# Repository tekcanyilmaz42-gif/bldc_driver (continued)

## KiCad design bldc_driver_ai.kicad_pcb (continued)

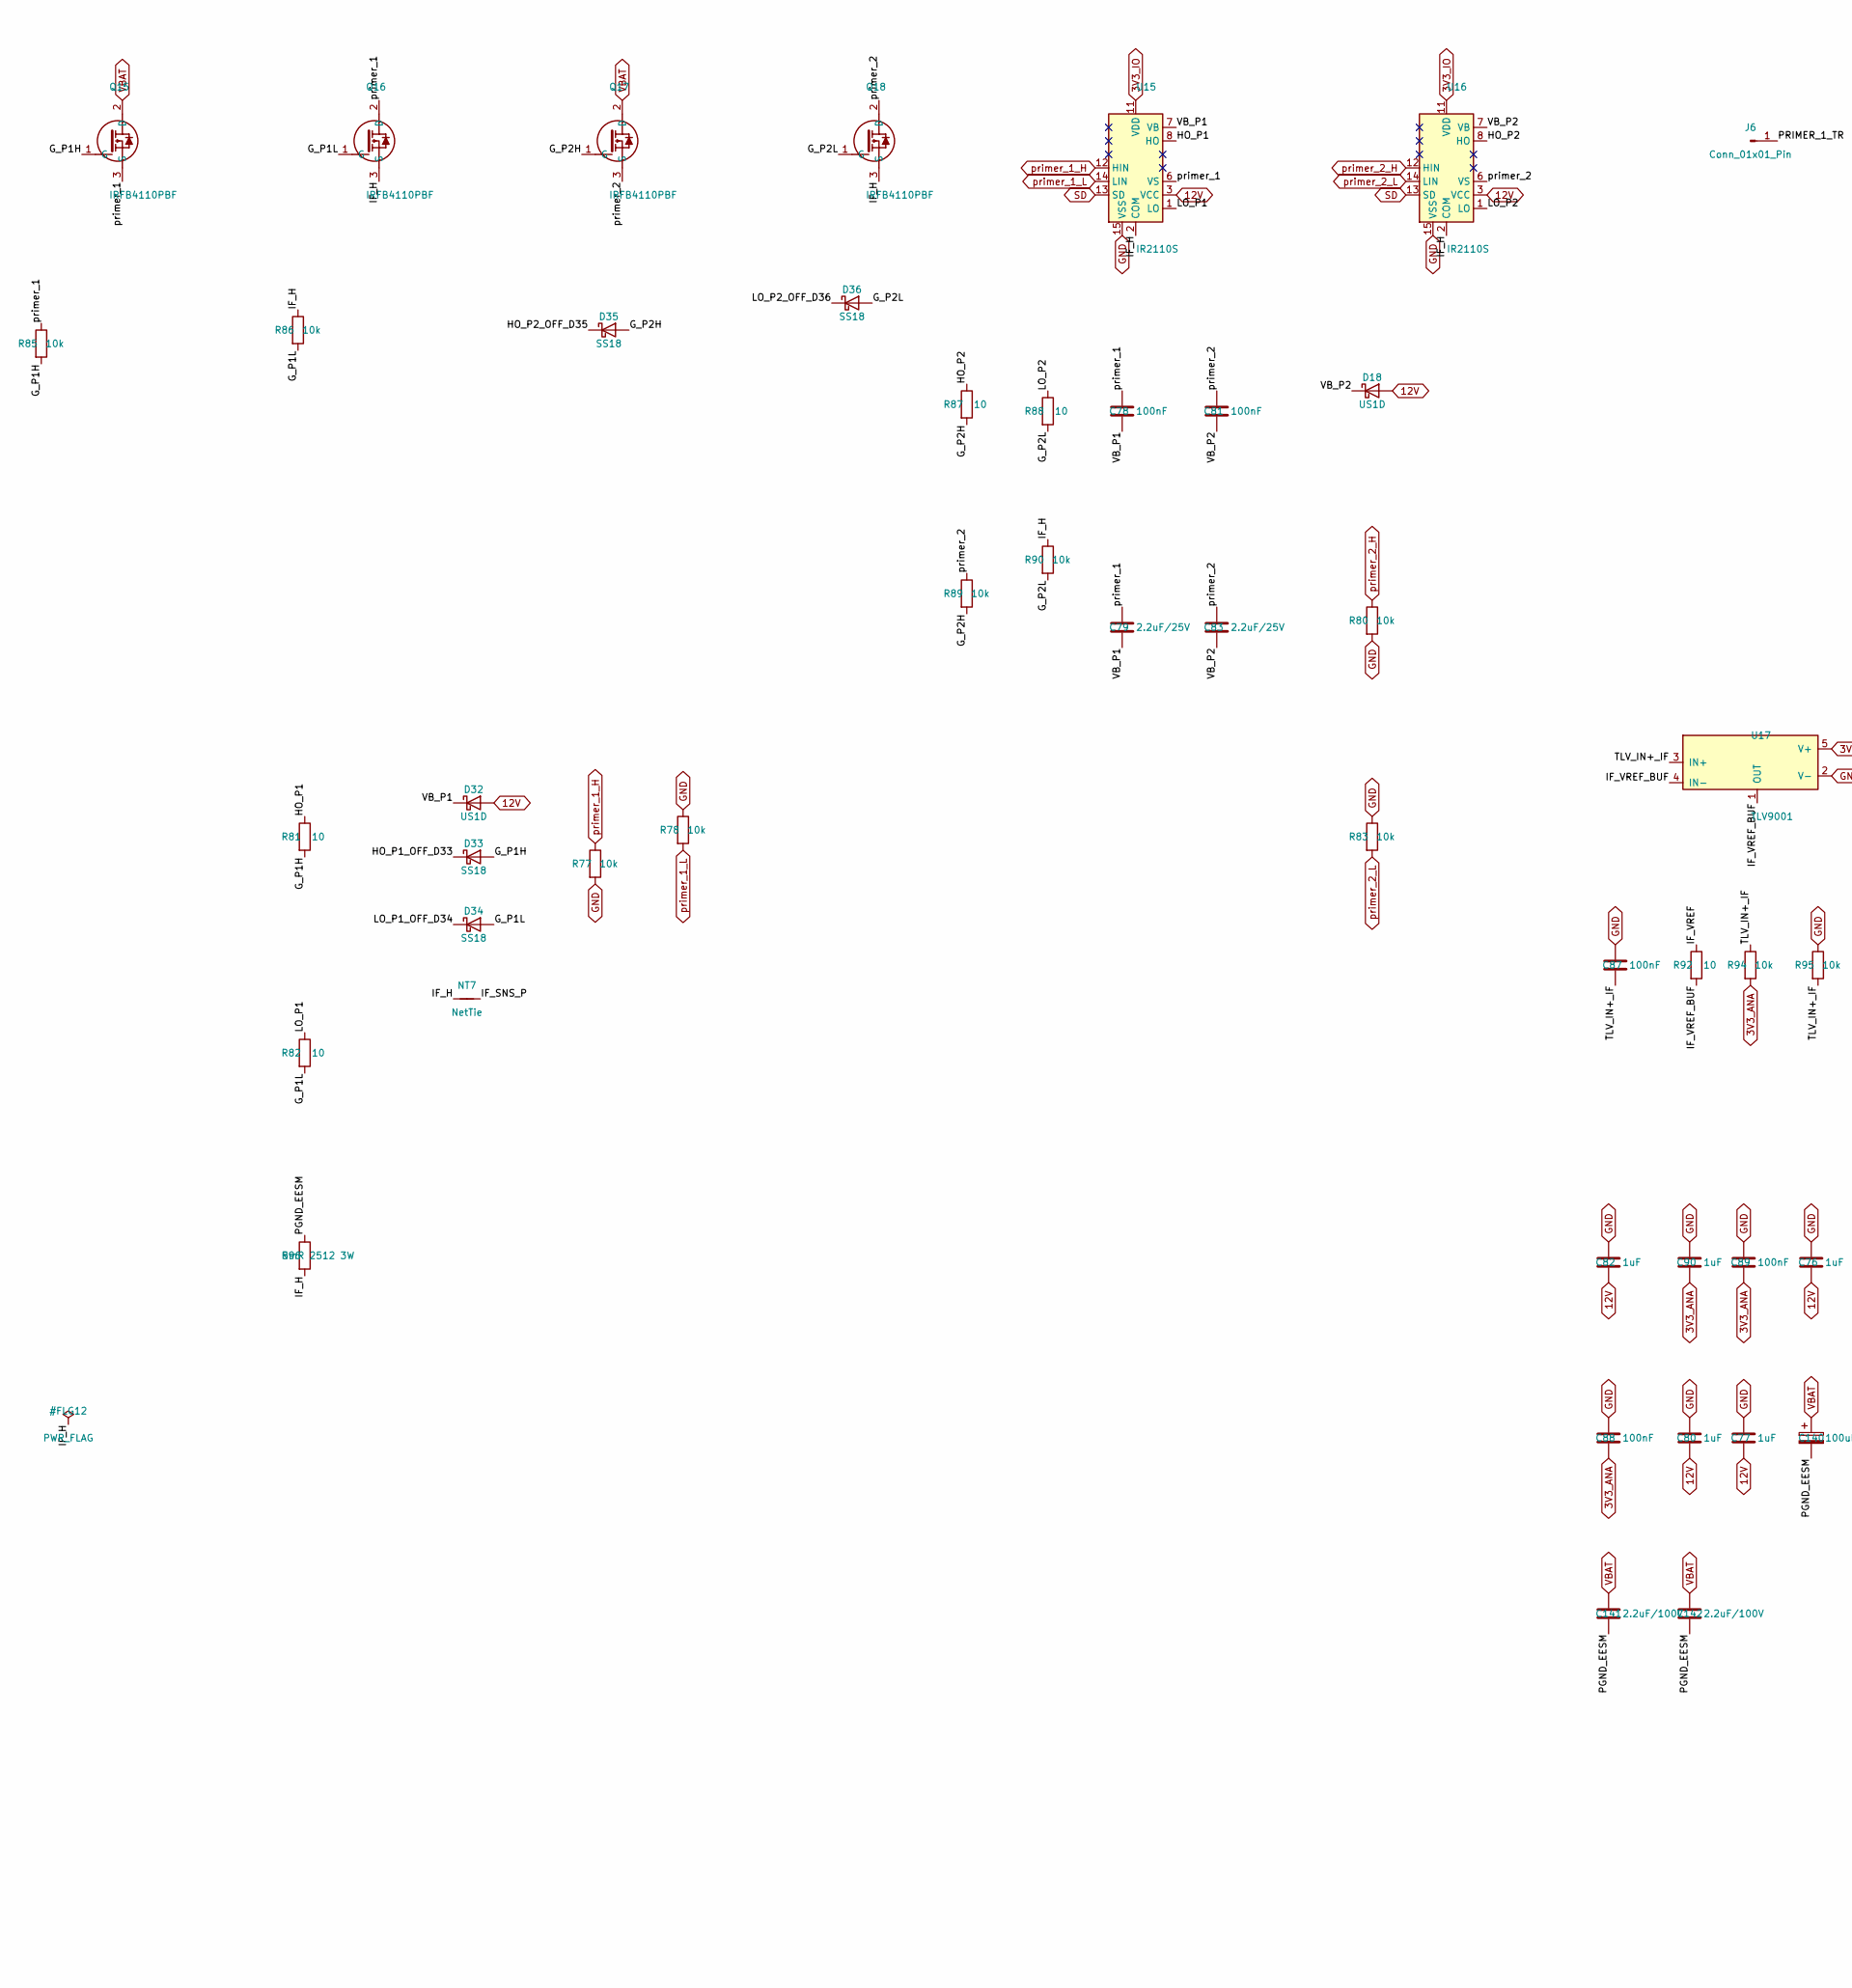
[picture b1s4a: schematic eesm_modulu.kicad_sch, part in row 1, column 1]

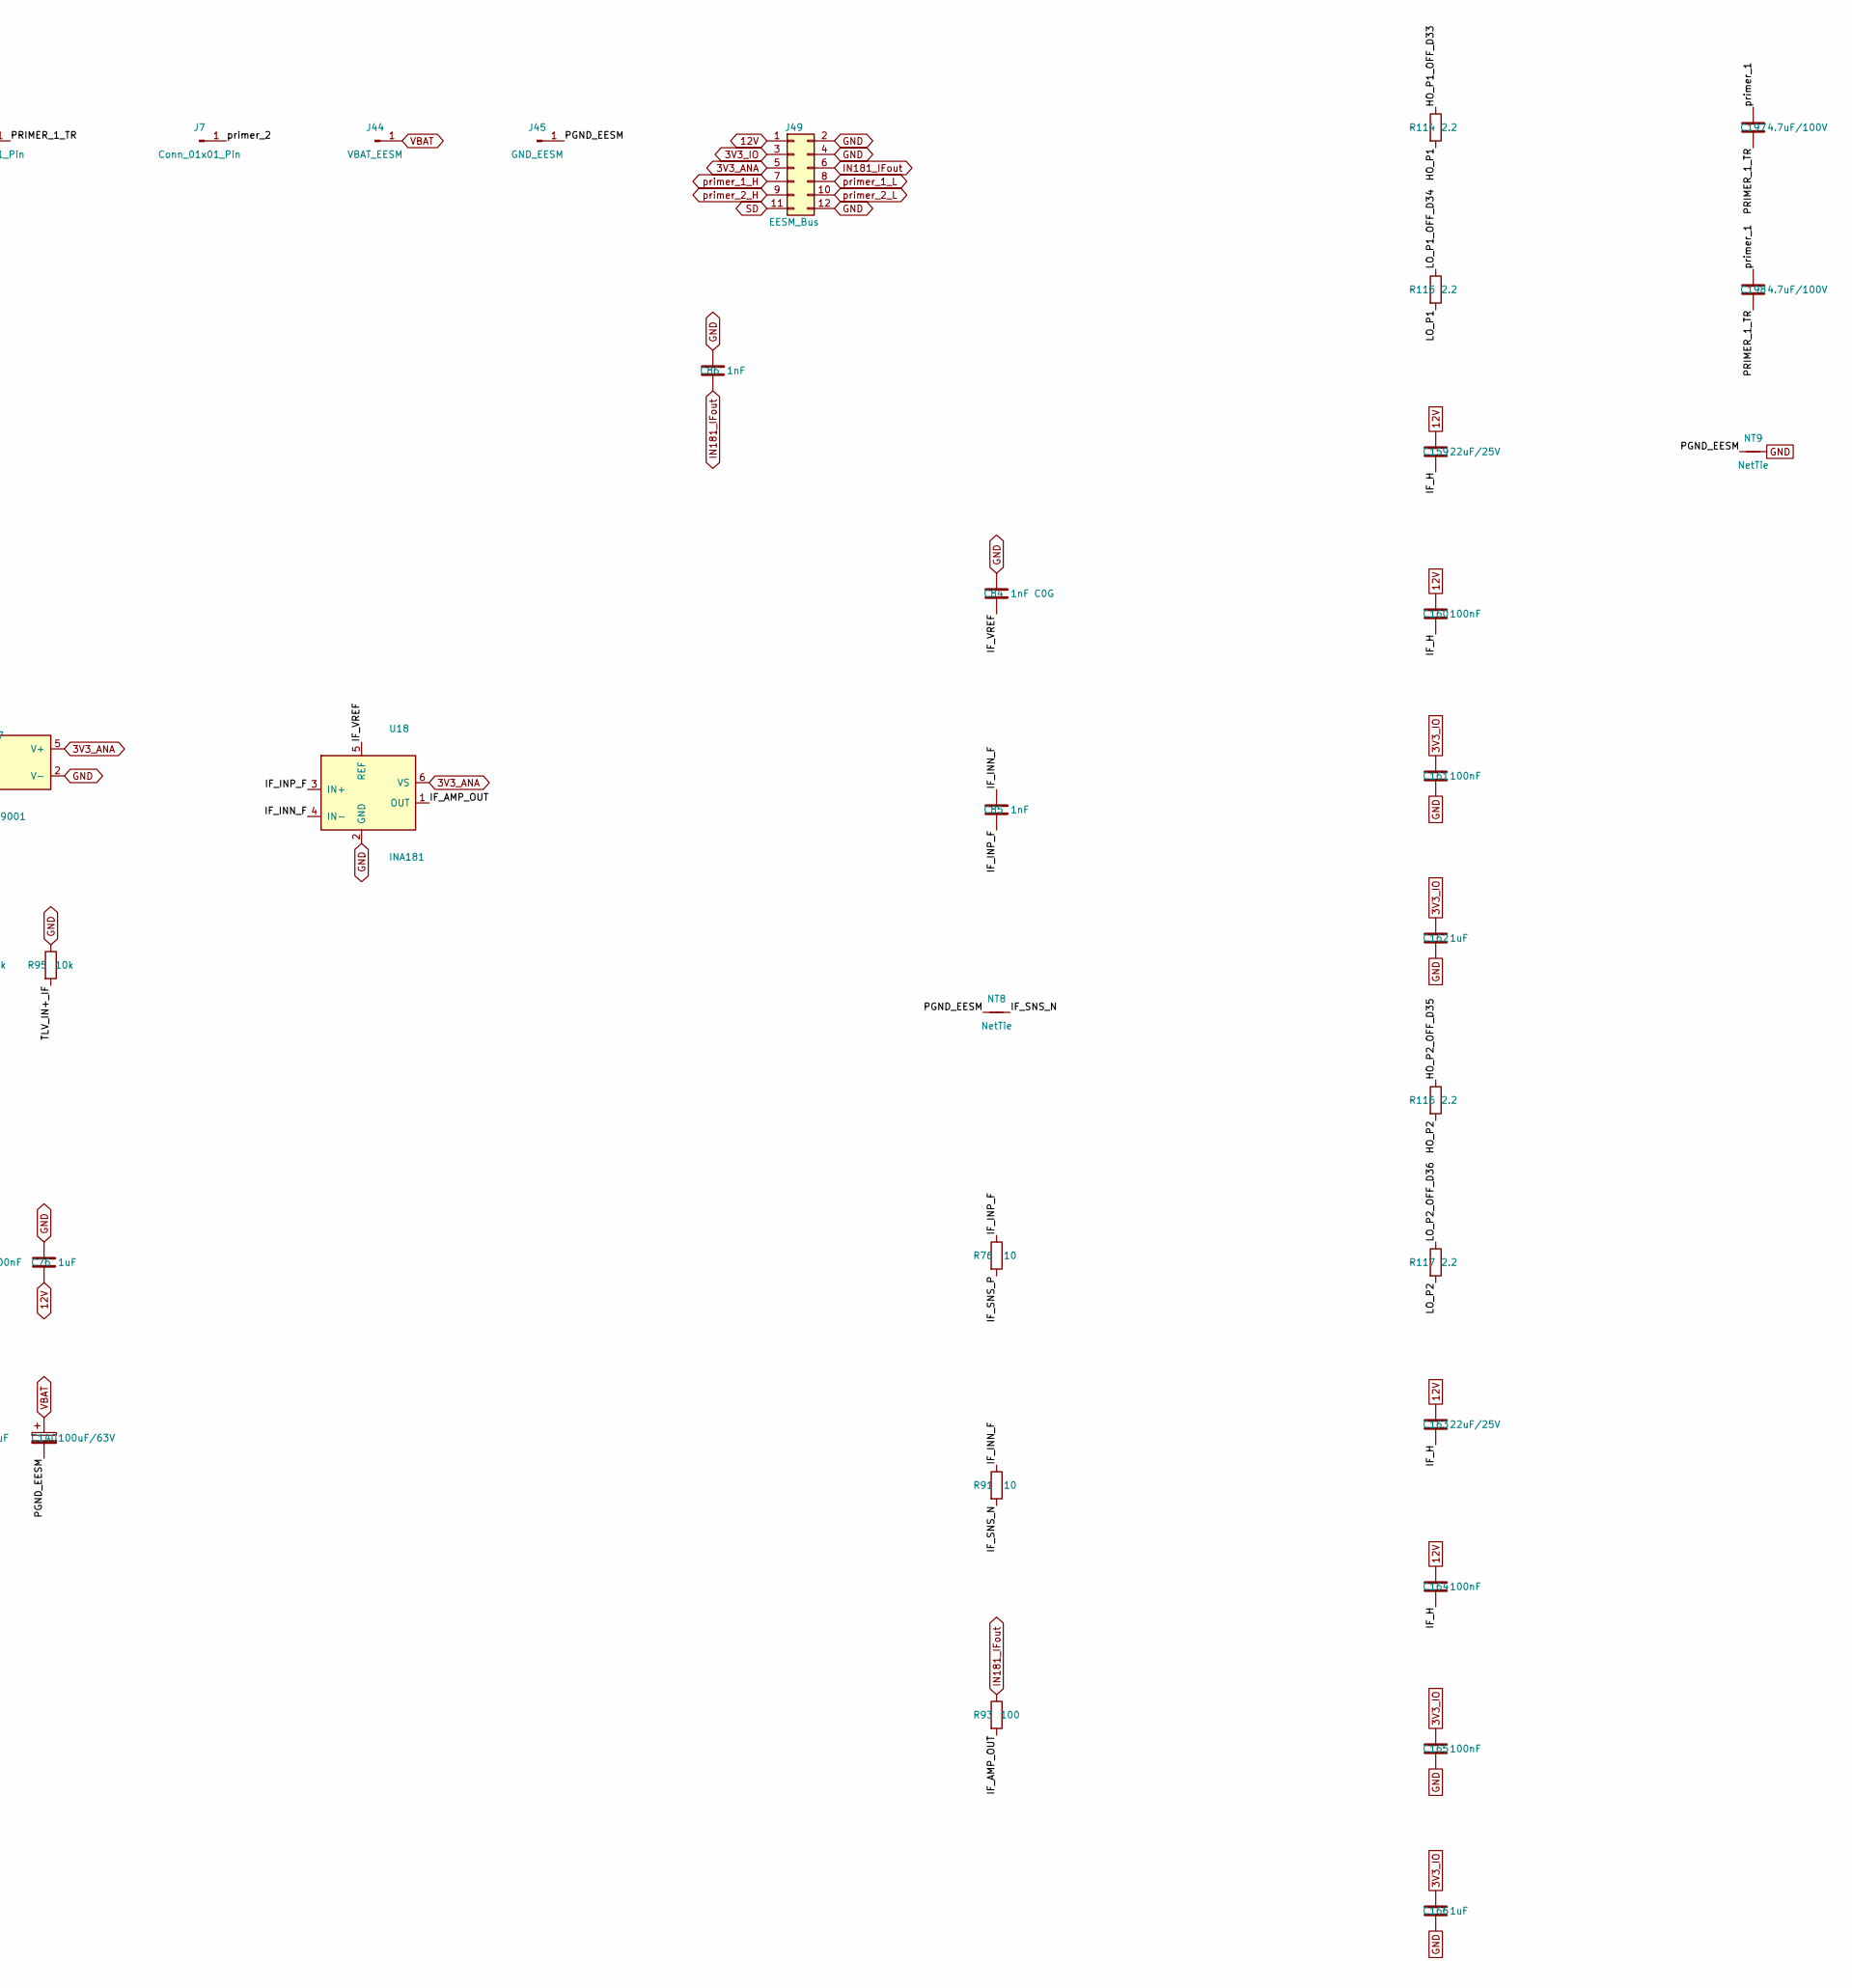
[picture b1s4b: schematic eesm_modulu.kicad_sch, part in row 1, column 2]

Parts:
C76, C77, C80, C82, C90, C162, C166: 1uF; C_0603_1608Metric
C78, C81, C87, C88, C89, C160, C161, C164, C165: 100nF; C_0603_1608Metric
C79, C83: 2.2uF/25V; C_1206_3216Metric; MPN CL31B225KAHNNNE
C84: 1nF C0G; C_0603_1608Metric
C85, C86: 1nF; C_0603_1608Metric
C140: 100uF/63V; CP_Elec_10x10.5
C141, C142: 2.2uF/100V; C_1206_3216Metric
C159, C163: 22uF/25V; C_1206_3216Metric; MPN CL31A226KAHNNNE
C197, C198: 4.7uF/100V; C_1210_3225Metric; MPN GRM32ER72A475KA12L
D18, D32: US1D; D_SMA; MPN US1D-13-F
D33, D34, D35, D36: SS18; D_SMA
J6, J7: Conn_01x01_Pin; SolderWire-2.5sqmm_1x01_D2.4mm_OD4.4mm
J44: VBAT_EESM; SolderWire-2.5sqmm_1x01_D2.4mm_OD4.4mm
J45: GND_EESM; SolderWire-2.5sqmm_1x01_D2.4mm_OD4.4mm
J49: EESM_Bus; PinHeader_2x06_P2.54mm_Vertical
NT7, NT8: NetTie; NetTie-2_SMD_Pad0.5mm
NT9: NetTie; NetTie-2_SMD_Pad2.0mm
Q15, Q16, Q17, Q18: IRFB4110PBF; TO-220-3_Vertical
R76, R81, R82, R87, R88, R91, R92: 10; R_0805_2012Metric
R77, R78, R80, R83, R85, R86, R89, R90, R94, R95: 10k; R_0603_1608Metric
R93: 100; R_0805_2012Metric
R96: 5mR 2512 3W; R_2512_6332Metric; MPN CSS2H-2512R-5L00F (Bourns) - dogrulanac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
R114, R115, R116, R117: 2.2; R_0603_1608Metric
U15, U16: IR2110S; SOIC-16W_7.5x10.3mm_P1.27mm
U17: TLV9001
U18: INA181

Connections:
3V3_ANA: C88.2, C89.2, C90.2, J49.5, R94.2, U17.5 (V+), U18.6 (VS); also elsewhere on the board
3V3_IO: C161.1, C162.1, C165.1, C166.1, J49.3, U15.11 (VDD), U16.11 (VDD); also elsewhere on the board
12V: C76.2, C77.2, C80.2, C82.2, C159.1, C160.1, C163.1, C164.1, D18.2 (A), D32.2 (A), J49.1, U15.3 (VCC), U16.3 (VCC); also elsewhere on the board
/Katman4_EESM_Modulu/G_P1H: D33.2 (A), Q15.1 (G), R81.2, R85.2
/Katman4_EESM_Modulu/G_P1L: D34.2 (A), Q16.1 (G), R82.2, R86.2
/Katman4_EESM_Modulu/G_P2H: D35.2 (A), Q17.1 (G), R87.2, R89.2
/Katman4_EESM_Modulu/G_P2L: D36.2 (A), Q18.1 (G), R88.2, R90.2
/Katman4_EESM_Modulu/HO_P1: R81.1, R114.2, U15.8 (HO)
/Katman4_EESM_Modulu/HO_P1_OFF_D33: D33.1 (K), R114.1
/Katman4_EESM_Modulu/HO_P2: R87.1, R116.2, U16.8 (HO)
/Katman4_EESM_Modulu/HO_P2_OFF_D35: D35.1 (K), R116.1
/Katman4_EESM_Modulu/IF_AMP_OUT: R93.2, U18.1 (OUT)
/Katman4_EESM_Modulu/IF_H: C159.2, C160.2, C163.2, C164.2, NT7.1, Q16.3 (S), Q18.3 (S), R86.1, R90.1, R96.2, U15.2 (COM), U16.2 (COM)
/Katman4_EESM_Modulu/IF_INN_F: C85.1, R91.1, U18.4 (IN-)
/Katman4_EESM_Modulu/IF_INP_F: C85.2, R76.1, U18.3 (IN+)
/Katman4_EESM_Modulu/IF_SNS_N: NT8.2, R91.2
/Katman4_EESM_Modulu/IF_SNS_P: NT7.2, R76.2
/Katman4_EESM_Modulu/IF_VREF: C84.2, R92.1, U18.5 (REF)
/Katman4_EESM_Modulu/IF_VREF_BUF: R92.2, U17.1 (OUT), U17.4 (IN-)
/Katman4_EESM_Modulu/LO_P1: R82.1, R115.2, U15.1 (LO)
/Katman4_EESM_Modulu/LO_P1_OFF_D34: D34.1 (K), R115.1
/Katman4_EESM_Modulu/LO_P2: R88.1, R117.2, U16.1 (LO)
/Katman4_EESM_Modulu/LO_P2_OFF_D36: D36.1 (K), R117.1
/Katman4_EESM_Modulu/PGND_EESM: C140.2, C141.2, C142.2, J45.1 (Pin_1_1), NT8.1, NT9.1, R96.1
/Katman4_EESM_Modulu/PRIMER_1_TR: C197.2, C198.2, J6.1 (Pin_1_1)
/Katman4_EESM_Modulu/TLV_IN+_IF: C87.2, R94.1, R95.2, U17.3 (IN+)
/Katman4_EESM_Modulu/VB_P1: C78.2, C79.2, D32.1 (K), U15.7 (VB)
/Katman4_EESM_Modulu/VB_P2: C81.2, C83.2, D18.1 (K), U16.7 (VB)
/Katman4_EESM_Modulu/primer_1: C78.1, C79.1, C197.1, C198.1, Q15.3 (S), Q16.2 (D), R85.1, U15.6 (VS)
/Katman4_EESM_Modulu/primer_2: C81.1, C83.1, J7.1 (Pin_1_1), Q17.3 (S), Q18.2 (D), R89.1, U16.6 (VS)
GND: C76.1, C77.1, C80.1, C82.1, C84.1, C86.1, C87.1, C88.1, C89.1, C90.1, C161.2, C162.2, C165.2, C166.2, J49.2, J49.4, J49.12, NT9.2, R77.2, R78.1, R80.2, R83.1, R95.1, U15.15 (VSS), U16.15 (VSS), U17.2 (V-), U18.2 (GND); also elsewhere on the board
IN181_IFout: C86.2, J49.6, R93.1; also elsewhere on the board
SD: J49.11, U15.13 (SD), U16.13 (SD); also elsewhere on the board
VBAT: C140.1, C141.1, C142.1, J44.1 (Pin_1_1), Q15.2 (D), Q17.2 (D); also elsewhere on the board
primer_1_H: J49.7, R77.1, U15.12 (HIN); also elsewhere on the board
primer_1_L: J49.8, R78.2, U15.14 (LIN); also elsewhere on the board
primer_2_H: J49.9, R80.1, U16.12 (HIN); also elsewhere on the board
primer_2_L: J49.10, R83.2, U16.14 (LIN); also elsewhere on the board

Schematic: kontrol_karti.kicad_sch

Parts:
C8: 10nF; C_0603_1608Metric
C9, C11: 100nF/100V; C_0805_2012Metric; MPN CL21B104KCFNNNE
C10, C16, C17, C22, C28, C29, C30, C35, C36, C37, C42, C45, C46, C100, C102, C103, C104, C105, C106, C136, C137, C143, C144, C199, C224: 100nF; C_0603_1608Metric
C12: 4.7nF; C_0603_1608Metric
C13, C20, C31, C38, C107: 1uF; C_0603_1608Metric
C14, C15: 10uF; C_0603_1608Metric
C18, C39, C40, C91, C93: 10uF/25V; C_1206_3216Metric
C19, C92, C94, C146: 22uF/10V; C_0805_2012Metric
C21, C25, C32: 1nF C0G; C_0603_1608Metric
C23, C26, C33: 220nF; C_0603_1608Metric
C24, C27, C34, C132, C133, C134, C173, C174, C175, C176, C177, C178: 1nF; C_0603_1608Metric
C43, C44, C99, C101: 27pF; C_0603_1608Metric
C135: 10uF/16V; C_0805_2012Metric
C138, C139: 2.2uF/100V; C_1206_3216Metric
C145: 4.7uF/10V; C_0805_2012Metric
D37: NUP2105L; SOT-23
D40, D41: SS18; D_SMA
D42: SS34; D_SMA
D43: SMAJ15A; D_SMA
Enkoder_soket1: Conn_01x05_Socket; PinHeader_1x05_P2.54mm_Vertical
F1: PTC 1.1A/33V; Fuse_1812_4532Metric
FB1: FerriteBead; C_0805_2012Metric
J8: CAN-bus; PinHeader_1x03_P2.54mm_Vertical
J23: USB_IN; USB_C_Receptacle_GCT_USB4105-xx-A_16P_TopMnt_Horizontal
J35: Pwr_U; PinSocket_1x03_P2.54mm_Vertical
J36: Ctrl_U; PinSocket_1x03_P2.54mm_Vertical
J37: Sense_U; PinHeader_1x02_P2.54mm_Vertical
J38: Pwr_V; PinSocket_1x03_P2.54mm_Vertical
J39: Ctrl_V; PinSocket_1x03_P2.54mm_Vertical
J40: Sense_V; PinHeader_1x02_P2.54mm_Vertical
J41: Pwr_W; PinSocket_1x03_P2.54mm_Vertical
J42: Ctrl_W; PinSocket_1x03_P2.54mm_Vertical
J43: Sense_W; PinHeader_1x02_P2.54mm_Vertical
J47: Riser_VBAT_GND; PinHeader_2x02_P2.54mm_Vertical
J48: EESM_Bus; PinSocket_2x06_P2.54mm_Vertical
J50: Kontaktor; PinHeader_1x04_P2.54mm_Vertical
J51: NTC_sogutucu; PinHeader_1x02_P2.54mm_Vertical
J52: Motor_Sicaklik; PinHeader_1x02_P2.54mm_Vertical
JICSPSoket1: Conn_01x05_Pin; PinHeader_1x05_P2.54mm_Vertical
JP1: CAN 120R; SolderJumper-2_P1.3mm_Open_RoundedPad1.0x1.5mm
L2: 33uH; L_Bourns_SRR1260; MPN SRR1260-330M
Q13, Q14: IRLML0100TRPBF; SOT-23
Q19, Q20: AO3400A; SOT-23
R4: 5.6k; R_0805_2012Metric
R5, R100: 100k; R_0603_1608Metric
R18: 20k; R_0603_1608Metric
R19: 1.05k 1%; R_0805_2012Metric
R20: 2.2; R_0603_1608Metric
R21: 100k; R_1206_3216Metric
R22: 60k; R_0603_1608Metric_Pad0.98x0.95mm_HandSolder
R23, R24, R33, R34, R39, R40, R68, R140, R142: 10k; R_0603_1608Metric
R25, R26, R27, R29, R30, R31, R35, R36, R37: 10; R_0805_2012Metric
R28, R32, R38, R69: 100; R_0805_2012Metric
R41, R42: 5.1k; R_0805_2012Metric
R57: 2.2k; R_0603_1608Metric
R66: 100k; R_0603_1608Metric_Pad0.98x0.95mm_HandSolder
R67: 4.7k; R_0805_2012Metric
R70, R72, R74: 1.5k; R_0805_2012Metric
R71, R73, R75: 1k; R_0805_2012Metric
R97: 0R; R_0805_2012Metric
R98: 470k; R_1206_3216Metric
R99: 27k; R_0603_1608Metric
R101: 120; R_0805_2012Metric
R139, R141: 100; R_0603_1608Metric
R143: 10k 0.1%; R_0603_1608Metric
R144: 1k; R_0603_1608Metric
R145: 2.2k 0.1%; R_0603_1608Metric
R146: 22k; R_0603_1608Metric
SW1: SW_Push; SW_SPST_CK_RS282G05A3
U4: ADuM1201; ADuM1201_LP
U5: CH340G; CH340G_LP
U6: dsPIC33CK256MP508; LQFP-80_12x12mm_P0.5mm
U7, U12, U14: INA181; INA181_LP
U8, U19, U20: LDL1117S33R; NCP1117
U9: MIC2128; MIC2128_LP
U10, U11, U13: TLV9001; TLV9001_LP
U21: LDL1117S50R; NCP1117
U22: TJA1051; TJA1051_LP
U23: SP0503BAHT; SOT-143
U24: USBLC6-2SC6; SOT-23-6
U25: TSR 1-2450; Converter_DCDC_TRACO_TSR-1_THT
Y2, Y3: 12MHz Kristal; AS-12.000-18-3030-EXT-SMD-TR

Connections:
3V3_ANA: C16.2, C17.2, C20.2, C29.2, C30.2, C31.2, C36.2, C37.2, C38.2, C94.2, FB1.1, J48.5, R23.2, R33.2, R39.2, R143.1, R145.1, U7.6 (VS), U10.5 (V+), U11.5 (V+), U12.6 (VS), U13.5 (V+), U14.6 (VS), U20.2 (VO), U20.4 (TAB); also elsewhere on the board
3V3_IO: C19.2, C137.1, C143.1, Enkoder_soket1.1, J35.1, J38.1, J41.1, J48.3, R57.1, R70.1, R72.1, R74.1, U4.8 (VDD2), U8.2 (VO), U8.4 (TAB), U22.5 (VIO); also elsewhere on the board
3V3_MCU: C92.2, C102.2, C103.2, C104.2, C105.2, JICSPSoket1.2, R68.2, R100.2, U6.12 (VDD), U6.31 (VDD), U6.51 (VDD), U6.71 (VDD), U19.2 (VO), U19.4 (TAB)
5V_CAN: C135.1, C136.1, U21.2 (VO), U21.4 (TAB), U22.3 (VCC)
5V_USB: C45.2, C46.2, C145.1, J23.A4 (VBUS), J23.A9 (VBUS), J23.B4 (VBUS), J23.B9 (VBUS), U4.1 (VDD1), U5.16 (VCC), U24.5 (VBUS)
12V: C12.2, C13.2, C18.2, C39.2, C40.2, C91.2, C93.2, D42.1 (K), J35.2, J38.2, J41.2, J48.1, L2.2, R18.2, U9.9 (EXTVDD), U21.3 (VI), U25.1 (IN); also elsewhere on the board
/Katman3_Kontrol_Karti/5V_SYS: C146.1, U8.3 (VI), U19.3 (VI), U20.3 (VI), U25.3 (OUT)
/Katman3_Kontrol_Karti/12V_EXT: D42.2 (A), D43.1 (K), F1.2
/Katman3_Kontrol_Karti/BUCK_BST: C10.2, U9.4 (BST)
/Katman3_Kontrol_Karti/BUCK_EN: R98.2, R99.1, U9.10 (EN)
/Katman3_Kontrol_Karti/BUCK_FB_DIV: R19.1, R97.2
/Katman3_Kontrol_Karti/BUCK_FREQ: R21.2, R22.2, U9.11 (FREQ)
/Katman3_Kontrol_Karti/BUCK_ILIM: R4.1, U9.2 (ILIM)
/Katman3_Kontrol_Karti/BUCK_PG: R100.1, U6.66 (RC10/RP58), U9.1 (PG)
/Katman3_Kontrol_Karti/BUCK_PVDD: C14.2, R20.1, U9.8 (PVDD)
/Katman3_Kontrol_Karti/BUCK_RIPPLE: C11.1, R5.2
/Katman3_Kontrol_Karti/BUCK_SS: C8.2, U9.12 (SS)
/Katman3_Kontrol_Karti/BUCK_SW: C10.1, C11.2, L2.1, Q13.3 (D), Q14.2 (S), R4.2, U9.3 (SW)
/Katman3_Kontrol_Karti/BUCK_VDD: C15.2, R20.2, U9.15 (VDD)
/Katman3_Kontrol_Karti/CANH: D37.1 (K), J8.2, R101.1, U22.7 (CANH)
/Katman3_Kontrol_Karti/CANL: D37.2 (K), J8.1, JP1.2 (B), U22.6 (CANL)
/Katman3_Kontrol_Karti/CAN_TERM: JP1.1 (A), R101.2
/Katman3_Kontrol_Karti/CH340_V3: C42.2, U5.4 (V3)
/Katman3_Kontrol_Karti/CH340_XI: C43.2, U5.7 (XI), Y2.1
/Katman3_Kontrol_Karti/CH340_XO: C44.2, U5.8 (XO), Y2.2
/Katman3_Kontrol_Karti/CH_RXD: U4.2 (VOA), U5.3 (RXD)
/Katman3_Kontrol_Karti/CH_TXD: U4.3 (VIB), U5.2 (TXD)
/Katman3_Kontrol_Karti/COIL_12V: D40.1 (K), D41.1 (K), F1.1, J50.1
/Katman3_Kontrol_Karti/CONT_EN: R139.1, U6.2 (RE0)
/Katman3_Kontrol_Karti/CONT_EN_G: Q19.1 (G), R139.2, R140.1
/Katman3_Kontrol_Karti/CONT_K: D40.2 (A), J50.2, Q19.3 (D)
/Katman3_Kontrol_Karti/DH: Q14.1 (G), U9.5 (DH)
/Katman3_Kontrol_Karti/DL: Q13.1 (G), U9.7 (DL)
/Katman3_Kontrol_Karti/Enkoder_A: C132.2, R71.2, U6.54 (RD5/RP69)
/Katman3_Kontrol_Karti/Enkoder_A_soket: Enkoder_soket1.2, R70.2, R71.1, U23.2 (K)
/Katman3_Kontrol_Karti/Enkoder_B: C133.2, R73.2, U6.53 (RD6/RP70)
/Katman3_Kontrol_Karti/Enkoder_B_soket: Enkoder_soket1.3, R72.2, R73.1, U23.3 (K)
/Katman3_Kontrol_Karti/Enkoder_Z: C134.2, R75.2, U6.52 (RD7/RP71)
/Katman3_Kontrol_Karti/Enkoder_Z_soket: Enkoder_soket1.4, R74.2, R75.1, U23.4 (K)
/Katman3_Kontrol_Karti/FB: C12.1, R5.1, R18.1, R19.2, U9.13 (FB)
/Katman3_Kontrol_Karti/IN181_Uout: C24.2, R28.1, U6.16 (RA0)
/Katman3_Kontrol_Karti/IN181_Vout: C27.2, R32.1, U6.18 (RA1), U6.33 (RC3/RP51)
/Katman3_Kontrol_Karti/IN181_Wout: C34.2, R38.1, U6.58 (RB7/RP39)
/Katman3_Kontrol_Karti/MCLR: JICSPSoket1.1, R69.1, U6.9 (MCLR)
/Katman3_Kontrol_Karti/MCLR_SW: C144.1, R68.1, R69.2, SW1.2
/Katman3_Kontrol_Karti/NTC_ADC: C199.1, R144.2, U6.20 (RA2)
/Katman3_Kontrol_Karti/NTC_HS: J51.1, R143.2, R144.1
/Katman3_Kontrol_Karti/NTC_MOT: J52.1, R145.2, R146.1
/Katman3_Kontrol_Karti/NTC_MOT_ADC: C224.1, R146.2, U6.40 (RC7/RP55)
/Katman3_Kontrol_Karti/OSCI_DSP: C101.2, U6.34 (OSCI/CLKI), Y3.2
/Katman3_Kontrol_Karti/OSCO_DSP: C99.2, U6.35 (OSCO/CLKO), Y3.1
/Katman3_Kontrol_Karti/PGC1: JICSPSoket1.5, U6.61 (RB9/RP41)
/Katman3_Kontrol_Karti/PGD1: JICSPSoket1.4, U6.60 (RB8/RP40)
/Katman3_Kontrol_Karti/PRE_EN: R141.1, U6.4 (RE1)
/Katman3_Kontrol_Karti/PRE_EN_G: Q20.1 (G), R141.2, R142.1
/Katman3_Kontrol_Karti/PRE_K: D41.2 (A), J50.3, Q20.3 (D)
/Katman3_Kontrol_Karti/RXD_DSP: U4.6 (VOB), U6.46 (RC8/RP56)
/Katman3_Kontrol_Karti/RXD_DSP_can: U6.68 (RD4/RP68), U22.4 (RXD)
/Katman3_Kontrol_Karti/TLV_IN+_u: C22.2, R23.1, R24.2, U10.3 (IN+)
/Katman3_Kontrol_Karti/TLV_IN+_v: C28.2, R33.1, R34.2, U11.3 (IN+)
/Katman3_Kontrol_Karti/TLV_IN+_w: C35.2, R39.1, R40.2, U13.3 (IN+)
/Katman3_Kontrol_Karti/TXD_DSP: U4.7 (VIA), U6.47 (RC9/RP57)
/Katman3_Kontrol_Karti/TXD_DSP_can: U6.69 (RD3/RP67), U22.1 (TXD)
/Katman3_Kontrol_Karti/USB_CC1: J23.A5 (CC1), R41.2
/Katman3_Kontrol_Karti/USB_CC2: J23.B5 (CC2), R42.2
/Katman3_Kontrol_Karti/USB_DM: J23.A7 (D-), J23.B7 (D-), U5.6 (UD-), U24.3 (I/O2), U24.4 (I/O2)
/Katman3_Kontrol_Karti/USB_DP: J23.A6 (D+), J23.B6 (D+), U5.5 (UD+), U24.1 (I/O1), U24.6 (I/O1)
/Katman3_Kontrol_Karti/U_AMP_OUT: R28.2, U7.1 (OUT)
/Katman3_Kontrol_Karti/U_INN_F: C23.1, C174.1, R27.1, U7.4 (IN-)
/Katman3_Kontrol_Karti/U_INP_F: C23.2, C173.1, R26.1, U7.3 (IN+)
/Katman3_Kontrol_Karti/U_VREF: C21.2, R25.1, U7.5 (REF)
/Katman3_Kontrol_Karti/U_VREF_BUF: R25.2, U10.1 (OUT), U10.4 (IN-)
/Katman3_Kontrol_Karti/V_AMP_OUT: R32.2, U12.1 (OUT)
/Katman3_Kontrol_Karti/V_BUS_SENSE: C100.2, R66.2, R67.2, U6.21 (RA3)
/Katman3_Kontrol_Karti/V_INN_F: C26.1, C176.1, R30.1, U12.4 (IN-)
/Katman3_Kontrol_Karti/V_INP_F: C26.2, C175.1, R29.1, U12.3 (IN+)
/Katman3_Kontrol_Karti/V_VREF: C25.2, R31.1, U12.5 (REF)
/Katman3_Kontrol_Karti/V_VREF_BUF: R31.2, U11.1 (OUT), U11.4 (IN-)
/Katman3_Kontrol_Karti/W_AMP_OUT: R38.2, U14.1 (OUT)
/Katman3_Kontrol_Karti/W_INN_F: C33.1, C178.1, R36.1, U14.4 (IN-)
/Katman3_Kontrol_Karti/W_INP_F: C33.2, C177.1, R35.1, U14.3 (IN+)
/Katman3_Kontrol_Karti/W_VREF: C32.2, R37.1, U14.5 (REF)
/Katman3_Kontrol_Karti/W_VREF_BUF: R37.2, U13.1 (OUT), U13.4 (IN-)
AVDD: C106.2, C107.2, FB1.2, U6.25 (AVDD)
GND: C8.1, C9.1, C13.1, C14.1, C15.1, C16.1, C17.1, C18.1, C19.1, C20.1, C21.1, C22.1, C24.1, C25.1, C27.1, C28.1, C29.1, C30.1, C31.1, C32.1, C34.1, C35.1, C36.1, C37.1, C38.1, C39.1, C40.1, C91.1, C92.1, C93.1, C94.1, C99.1, C100.1, C101.1, C102.1, C103.1, C104.1, C105.1, C106.1, C107.1, C132.1, C133.1, C134.1, C135.2, C136.2, C137.2, C138.2, C139.2, C143.2, C144.2, C146.2, C173.2, C174.2, C175.2, C176.2, C177.2, C178.2, C199.2, C224.2, D37.3 (A), D43.2 (A), Enkoder_soket1.5, J8.3, J35.3, J38.3, J41.3, J47.2, J47.4, J48.2, J48.4, J48.12, J50.4, J51.2, J52.2, JICSPSoket1.3, Q13.2 (S), Q19.2 (S), Q20.2 (S), R22.1, R24.1, R34.1, R40.1, R67.1, R97.1, R99.2, R140.2, R142.2, SW1.1, U4.5 (GND2), U6.11 (VSS), U6.26 (AVSS), U6.32 (VSS), U6.50 (VSS), U6.70 (VSS), U7.2 (GND), U8.1 (GND/ADJ), U9.6 (PGND), U9.14 (AGND), U9.17 (EP), U10.2 (V-), U11.2 (V-), U12.2 (GND), U13.2 (V-), U14.2 (GND), U19.1 (GND/ADJ), U20.1 (GND/ADJ), U21.1 (GND/ADJ), U22.2 (GND), U22.8 (S), U23.1 (A), U25.2 (GND); also elsewhere on the board
GND_PC: C42.1, C43.1, C44.1, C45.1, C46.1, C145.2, J23.A1 (GND), J23.A12 (GND), J23.B1 (GND), J23.B12 (GND), J23.SH (SHIELD), R41.1, R42.1, U4.4 (GND1), U5.1 (GND), U24.2 (GND)
G_UH_IN: J36.1, U6.1 (RB14/RP46); also elsewhere on the board
G_UL_IN: J36.3, U6.3 (RB15/RP47); also elsewhere on the board
G_VH_IN: J39.1, U6.78 (RB12/RP44); also elsewhere on the board
G_VL_IN: J39.3, U6.80 (RB13/RP45); also elsewhere on the board
G_WH_IN: J42.1, U6.75 (RB10/RP42); also elsewhere on the board
G_WL_IN: J42.3, U6.76 (RB11/RP43); also elsewhere on the board
IN181_IFout: J48.6, U6.23 (RA4); also elsewhere on the board
SD: J36.2, J39.2, J42.2, J48.11, R57.2, U6.72 (RD2/RP66); also elsewhere on the board
U_SNS_N: J37.2, R27.2; also elsewhere on the board
U_SNS_P: J37.1, R26.2; also elsewhere on the board
VBAT: C9.2, C138.1, C139.1, J47.1, J47.3, Q14.3 (D), R21.1, R66.1, R98.1, U9.16 (VIN); also elsewhere on the board
V_SNS_N: J40.2, R30.2; also elsewhere on the board
V_SNS_P: J40.1, R29.2; also elsewhere on the board
W_SNS_N: J43.2, R36.2; also elsewhere on the board
W_SNS_P: J43.1, R35.2; also elsewhere on the board
primer_1_H: J48.7, U6.73 (RD1/RP65); also elsewhere on the board
primer_1_L: J48.8, U6.74 (RD0/RP64); also elsewhere on the board
primer_2_H: J48.9, U6.63 (RC4/RP52); also elsewhere on the board
primer_2_L: J48.10, U6.65 (RC5/RP53); also elsewhere on the board

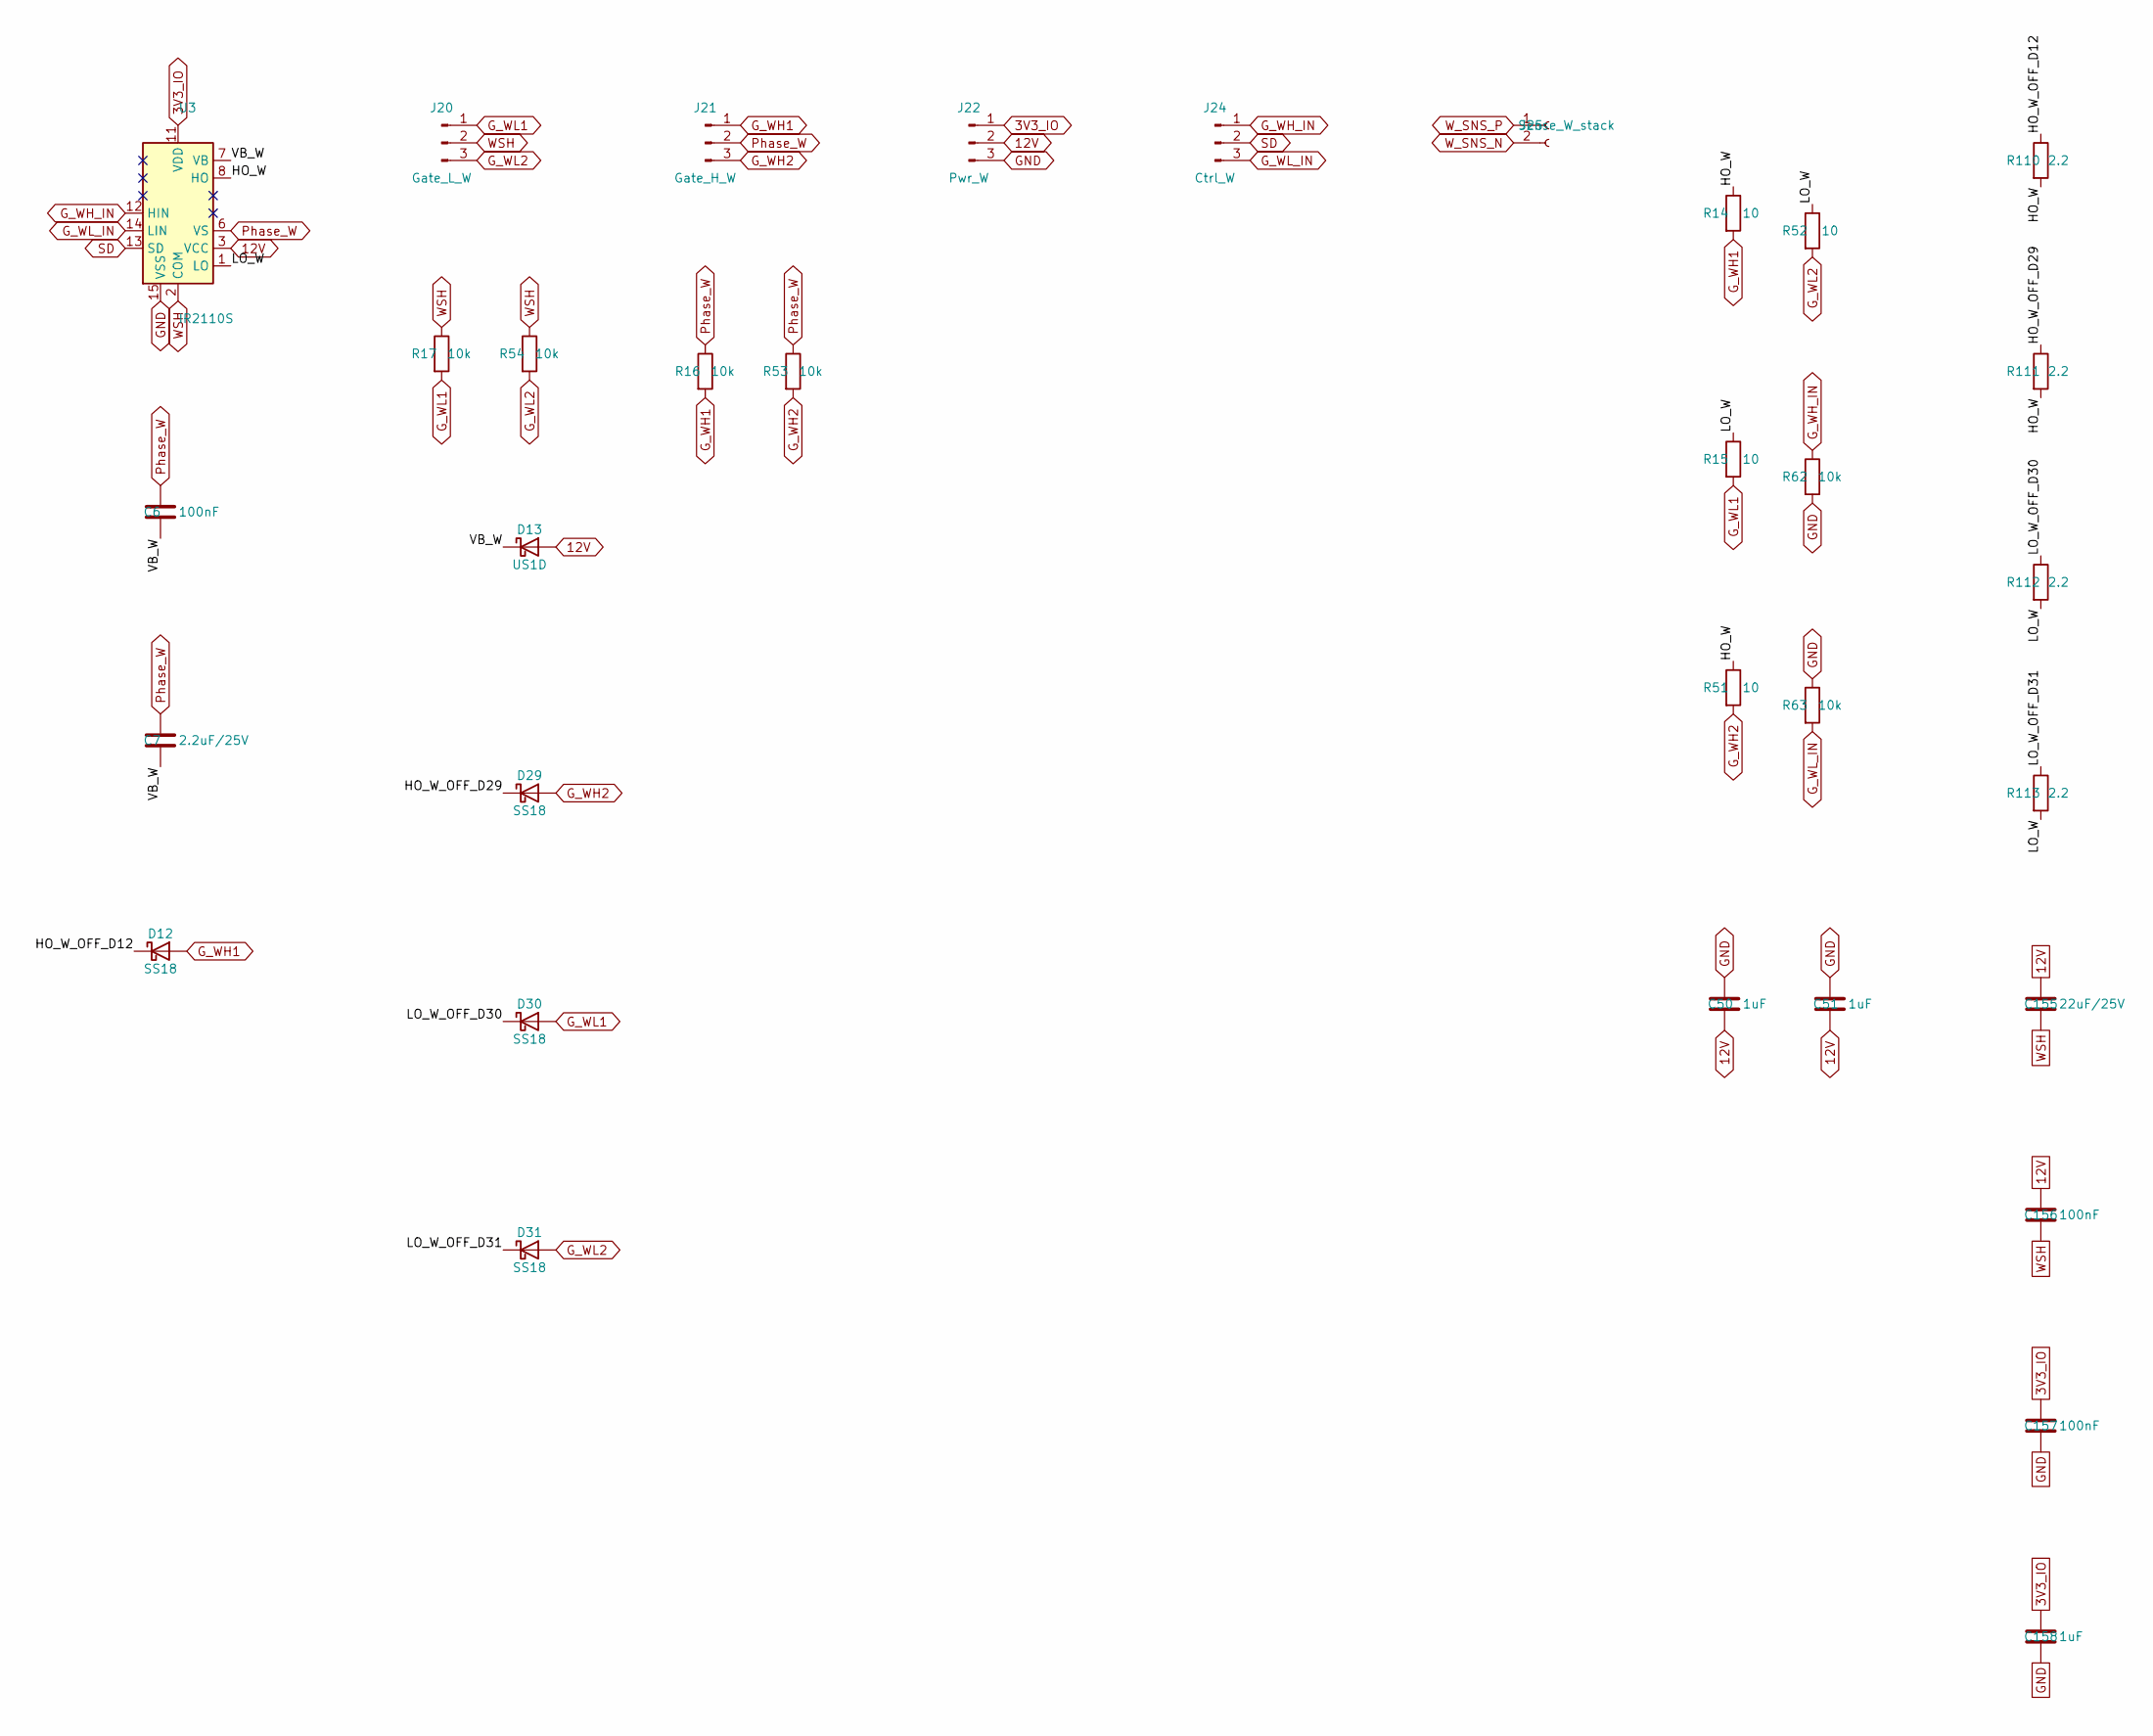
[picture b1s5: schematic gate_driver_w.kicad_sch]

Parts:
C6, C156, C157: 100nF; C_0603_1608Metric
C7: 2.2uF/25V; C_1206_3216Metric; MPN CL31B225KAHNNNE
C50, C51, C158: 1uF; C_0603_1608Metric
C155: 22uF/25V; C_1206_3216Metric; MPN CL31A226KAHNNNE
D12, D29, D30, D31: SS18; D_SMA
D13: US1D; D_SMA; MPN US1D-13-F
J20: Gate_L_W; PinHeader_1x03_P2.54mm_Vertical
J21: Gate_H_W; PinHeader_1x03_P2.54mm_Vertical
J22: Pwr_W; PinHeader_1x03_P2.54mm_Vertical
J24: Ctrl_W; PinHeader_1x03_P2.54mm_Vertical
J25: Sense_W_stack; PinSocket_1x02_P2.54mm_Vertical
R14, R15, R51, R52: 10; R_0805_2012Metric
R16, R17, R53, R54, R62, R63: 10k; R_0603_1608Metric
R110, R111, R112, R113: 2.2; R_0603_1608Metric
U3: IR2110S; SOIC-16W_7.5x10.3mm_P1.27mm

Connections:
3V3_IO: C157.1, C158.1, J22.1, U3.11 (VDD); also elsewhere on the board
12V: C50.2, C51.2, C155.1, C156.1, D13.2 (A), J22.2, U3.3 (VCC); also elsewhere on the board
/Katman2_GateDriver_W/HO_W: R14.1, R51.1, R110.2, R111.2, U3.8 (HO)
/Katman2_GateDriver_W/HO_W_OFF_D12: D12.1 (K), R110.1
/Katman2_GateDriver_W/HO_W_OFF_D29: D29.1 (K), R111.1
/Katman2_GateDriver_W/LO_W: R15.1, R52.1, R112.2, R113.2, U3.1 (LO)
/Katman2_GateDriver_W/LO_W_OFF_D30: D30.1 (K), R112.1
/Katman2_GateDriver_W/LO_W_OFF_D31: D31.1 (K), R113.1
/Katman2_GateDriver_W/VB_W: C6.2, C7.2, D13.1 (K), U3.7 (VB)
GND: C50.1, C51.1, C157.2, C158.2, J22.3, R62.2, R63.1, U3.15 (VSS); also elsewhere on the board
G_WH1: D12.2 (A), J21.1, R14.2, R16.2; also elsewhere on the board
G_WH2: D29.2 (A), J21.3, R51.2, R53.2; also elsewhere on the board
G_WH_IN: J24.1, R62.1, U3.12 (HIN); also elsewhere on the board
G_WL1: D30.2 (A), J20.1, R15.2, R17.2; also elsewhere on the board
G_WL2: D31.2 (A), J20.3, R52.2, R54.2; also elsewhere on the board
G_WL_IN: J24.3, R63.2, U3.14 (LIN); also elsewhere on the board
Phase_W: C6.1, C7.1, J21.2, R16.1, R53.1, U3.6 (VS); also elsewhere on the board
SD: J24.2, U3.13 (SD); also elsewhere on the board
WSH: C155.2, C156.2, J20.2, R17.1, R54.1, U3.2 (COM); also elsewhere on the board
W_SNS_N: J25.2; also elsewhere on the board
W_SNS_P: J25.1; also elsewhere on the board
